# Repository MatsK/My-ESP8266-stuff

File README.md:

# My-ESP8266-stuff

## Concept

### Breakout board
The Breakout board is for the ESP-01 version of the ESP8266 and make it easy to connect a ESP-01 to a lab board.

### Programmer
The programmer board is used togheter with a 3,3 volt, USB-serial device.

### USB Power to lab board
This USB power for lab boards has a auto reset fuse that ensure that if it is shorten it will not destroy the USB port on the computer.

## Files:

### My ESP-01 Breakout board
- ESP8266_ESP-01_Breakout_2015-11-16 (.sch/.brd)

### ESP-12 Breakout SMT
- ESP-12_Breakout_SMT (.sch/.brd)

### ESP-01 Programmer
- ESP8266-Programmer_2015-11-16 (.sch/.brd)

### USB Micro Power to lab board
- USB_Micro_Power_to_lab_board_2015-11-16 (.sch/.brd)

## Picture of the different PCB
### My ESP-01 Breakout board

## ESP-12 Breakout SMT board

### ESP-01 Programmer

### USB Micro Power to lab board

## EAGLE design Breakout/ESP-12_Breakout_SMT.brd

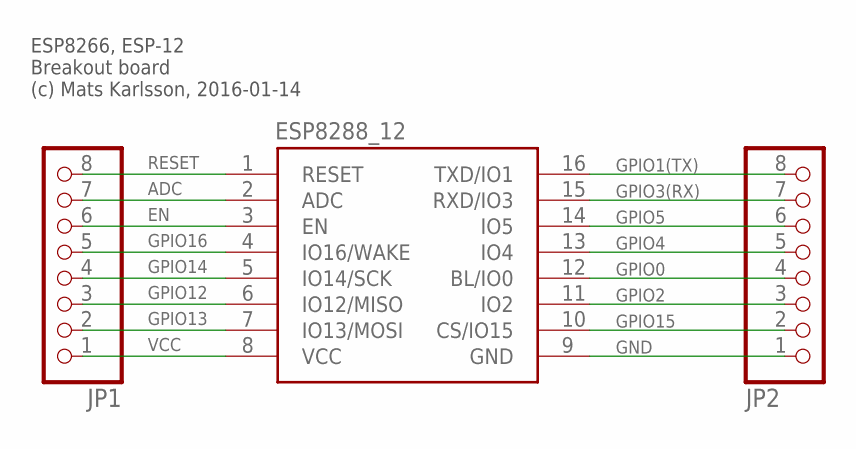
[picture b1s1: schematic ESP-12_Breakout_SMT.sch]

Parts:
ESP8288_12: ESP8266-12
JP1, JP2: PINHD-1X81X08_SMT; 1X08_SMT

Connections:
ADC: ESP8288_12.2 (ADC), JP1.7
EN: ESP8288_12.3 (EN), JP1.6
GND: ESP8288_12.9 (GND), JP2.1
GPIO0: ESP8288_12.12 (BL/IO0), JP2.4
GPIO1(TX): ESP8288_12.16 (TXD/IO1), JP2.8
GPIO2: ESP8288_12.11 (IO2), JP2.3
GPIO3(RX): ESP8288_12.15 (RXD/IO3), JP2.7
GPIO4: ESP8288_12.13 (IO4), JP2.5
GPIO5: ESP8288_12.14 (IO5), JP2.6
GPIO12: ESP8288_12.6 (IO12/MISO), JP1.3
GPIO13: ESP8288_12.7 (IO13/MOSI), JP1.2
GPIO14: ESP8288_12.5 (IO14/SCK), JP1.4
GPIO15: ESP8288_12.10 (CS/IO15), JP2.2
GPIO16: ESP8288_12.4 (IO16/WAKE), JP1.5
RESET: ESP8288_12.1 (RESET), JP1.8
VCC: ESP8288_12.8 (VCC), JP1.1

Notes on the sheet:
ESP8266, ESP-12 Breakout board (c) Mats Karlsson, 2016-01-14

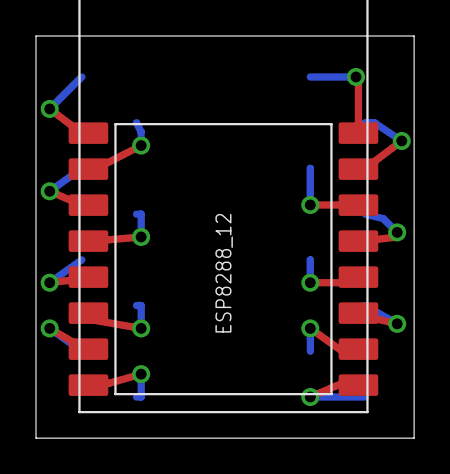
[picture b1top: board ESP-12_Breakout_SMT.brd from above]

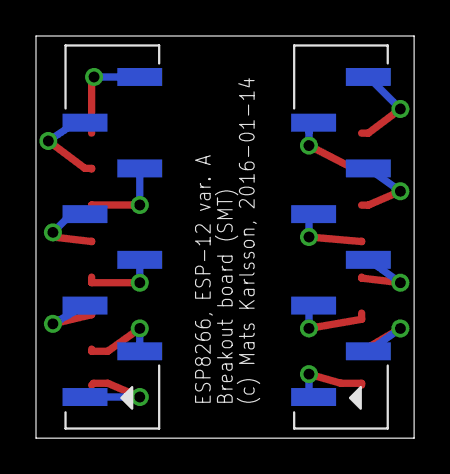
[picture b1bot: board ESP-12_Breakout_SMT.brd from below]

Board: 2 copper layers, 21.0 x 22.3 mm, 3 parts (2 on the bottom side), 16 nets.

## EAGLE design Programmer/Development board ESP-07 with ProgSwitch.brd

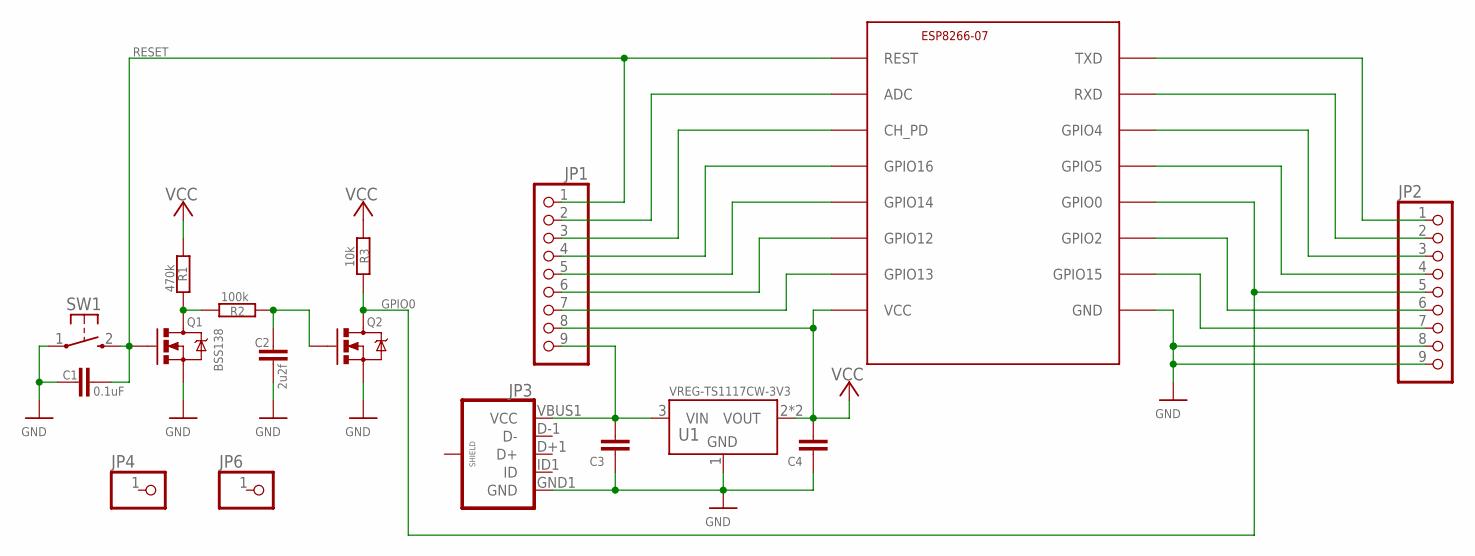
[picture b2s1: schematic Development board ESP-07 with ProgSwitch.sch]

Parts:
C1: 0.1uF; C025-024X044
C2: 2u2f; C025-024X044
C3, C4: C-EU025-024X044; C025-024X044
ESP8266-07: ESP8266-07; ESP-07
JP1, JP2: PINHD-1X91X09_SMT; 1X09_SMT
JP3: USB_MICROB_PLUGCONN-11752; USB-B-MICRO-SMD_V03
JP4, JP6: PINHD-1X1; 1X01
Q1, Q2: BSS138; SOT23-3
R1: 470k; R1206
R2: 100k; R1206
R3: 10k; R1206
SW1: KSS-2EG4430
U1: VREG-TS1117CW-3V3; SOT223

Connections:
GND: C1.1, C2.1, C3.1, C4.1, ESP8266-07.GND, JP2.8, JP2.9, JP3.GND1 (GND), Q1.2 (S), Q2.2 (S), SW1.1, U1.1 (GND)
GPIO0: ESP8266-07.GPIO0, JP2.5, Q2.3 (D), R3.2
unnamed: ESP8266-07.TXD, JP2.1
unnamed: ESP8266-07.RXD, JP2.2
unnamed: Q1.3 (D), R1.1, R2.1
unnamed: C2.2, Q2.1 (G), R2.2
unnamed: ESP8266-07.GPIO5, JP2.4
unnamed: ESP8266-07.VCC, JP1.8
unnamed: ESP8266-07.GPIO2, JP2.6
unnamed: ESP8266-07.GPIO15, JP2.7
unnamed: ESP8266-07.ADC, JP1.2
unnamed: ESP8266-07.CH_PD, JP1.3
unnamed: ESP8266-07.GPIO16, JP1.4
unnamed: ESP8266-07.GPIO14, JP1.5
unnamed: ESP8266-07.GPIO12, JP1.6
unnamed: C3.2, JP1.9, JP3.VBUS1 (VCC), U1.3 (VIN)
unnamed: ESP8266-07.GPIO13, JP1.7
unnamed: ESP8266-07.GPIO4, JP2.3
RESET: C1.2, ESP8266-07.REST, JP1.1, Q1.1 (G), SW1.2 (S)
VCC: C4.2, R1.2, R3.1, U1.2 (VOUT), U1.4 (VOUT)

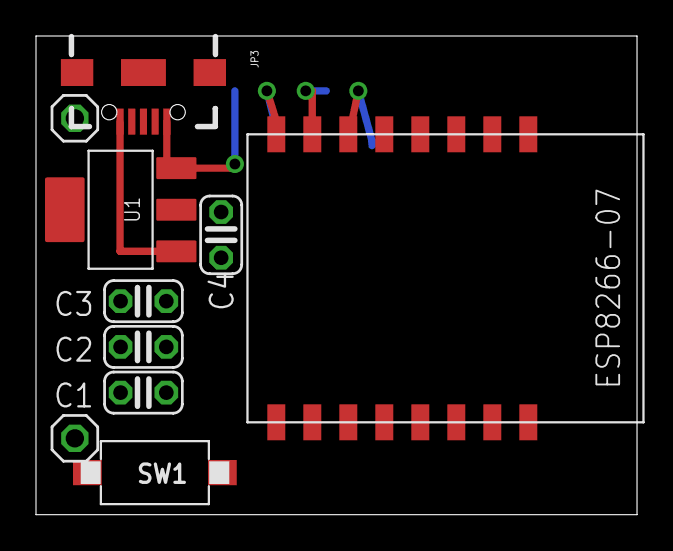
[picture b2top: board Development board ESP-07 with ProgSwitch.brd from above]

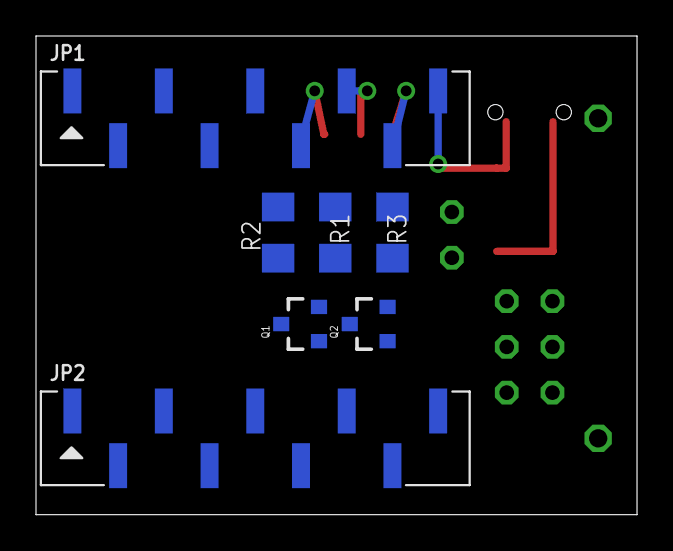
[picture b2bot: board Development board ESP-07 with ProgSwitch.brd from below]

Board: 2 copper layers, 33.4 x 26.6 mm, 17 parts (7 on the bottom side), 20 nets.

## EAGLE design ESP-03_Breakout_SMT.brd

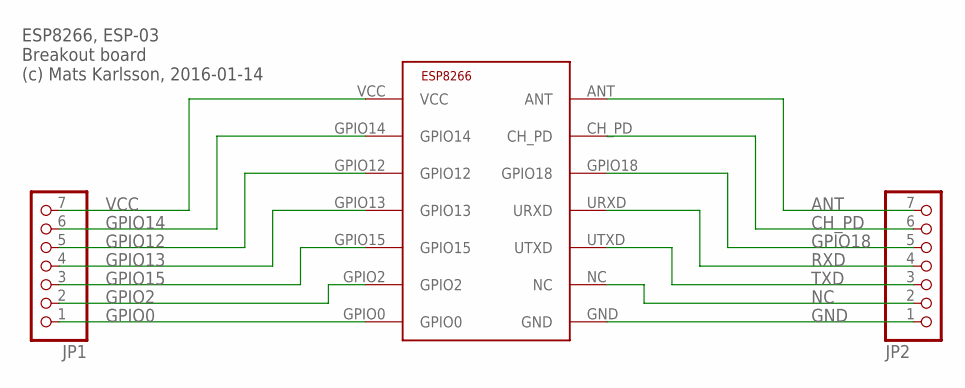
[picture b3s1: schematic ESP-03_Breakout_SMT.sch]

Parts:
JP1, JP2: PINHD-1X71X07_SMT; 1X07_SMT
U$1: ESP8266-03; ESP-03

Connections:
ANT: JP2.7, U$1.ANT
CH_PD: JP2.6, U$1.CH_PD
GND: JP2.1, U$1.GND
GPIO0: JP1.1, U$1.GPIO0
GPIO2: JP1.2, U$1.GPIO2
GPIO12: JP1.5, U$1.GPIO12
GPIO13: JP1.4, U$1.GPIO13
GPIO14: JP1.6, U$1.GPIO14
GPIO15: JP1.3, U$1.GPIO15
GPIO18: JP2.5, U$1.GPIO18
NC: JP2.2, U$1.NC
RXD: JP2.4, U$1.URXD
TXD: JP2.3, U$1.UTXD
VCC: JP1.7, U$1.VCC

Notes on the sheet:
ESP8266, ESP-03 Breakout board (c) Mats Karlsson, 2016-01-14

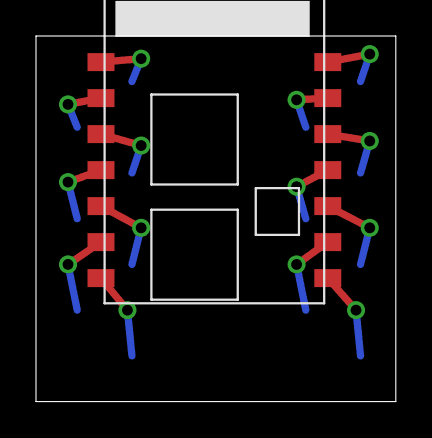
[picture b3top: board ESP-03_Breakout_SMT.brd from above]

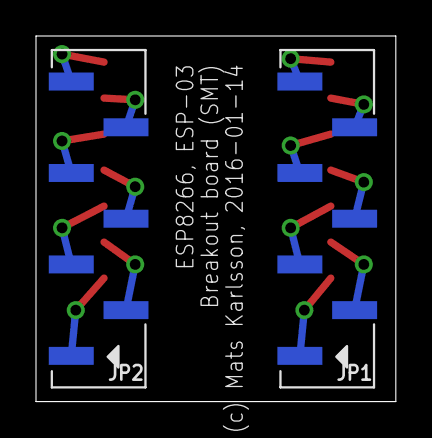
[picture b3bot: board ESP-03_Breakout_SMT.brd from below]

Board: 2 copper layers, 20.0 x 20.3 mm, 3 parts (2 on the bottom side), 14 nets.

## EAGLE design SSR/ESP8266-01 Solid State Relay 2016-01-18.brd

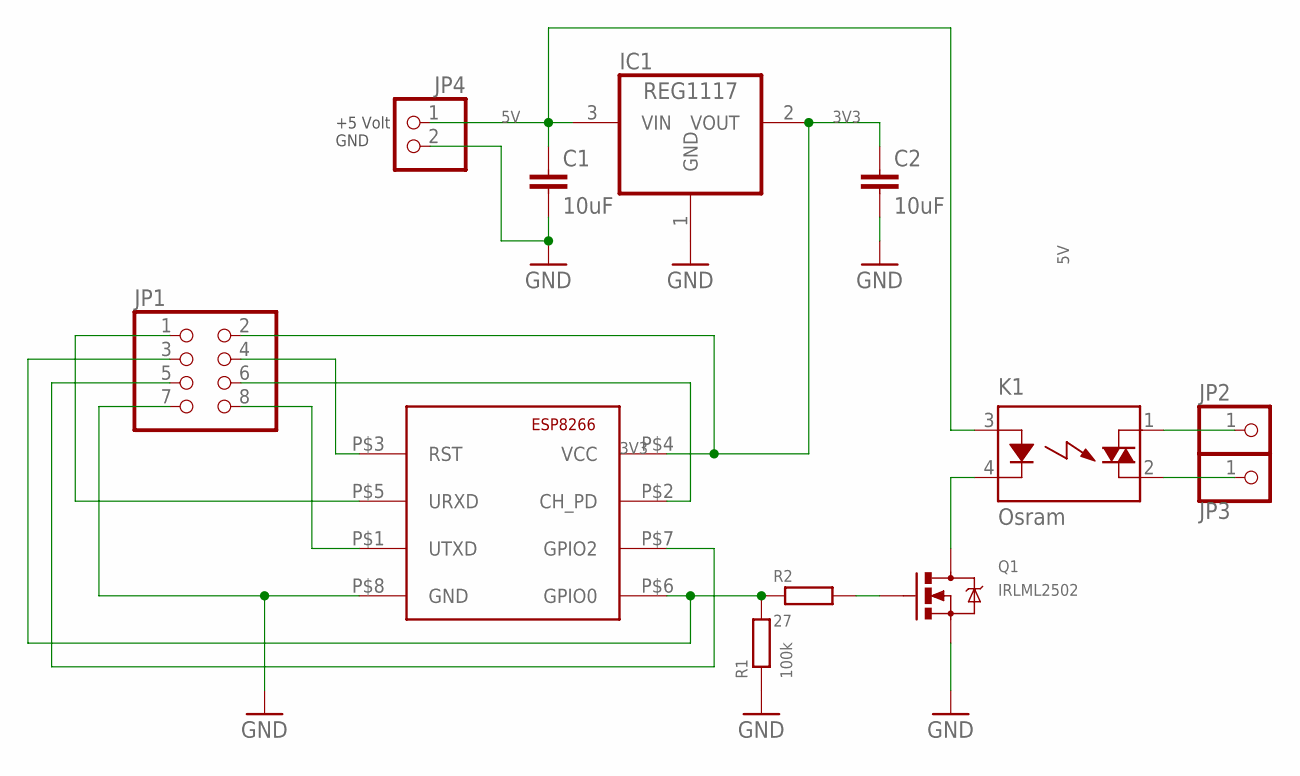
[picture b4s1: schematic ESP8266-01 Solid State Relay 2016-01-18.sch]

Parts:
C1, C2: 10uF; C1206
IC1: REG1117; SOT223
JP1: PINHD-2X4; 2X04
JP2, JP3: PINHD-1X1; 1X01
JP4: PINHD-1X2; 1X02
K1: Osram; S2XXEX
Q1: IRLML2502; SOT23-3
R1: 100k; R0805
R2: 27; R0805
U$1: ESP8266-01; ESP-01

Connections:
3V3: C2.1, IC1.2 (VOUT), JP1.2, U$1.P$4 (VCC)
5V: C1.1, IC1.3 (VIN), JP4.1, K1.3 (A)
GND: C1.2, C2.2, IC1.1 (GND), JP1.7, JP4.2, Q1.2 (S), R1.1, U$1.P$8 (GND)
unnamed: Q1.1 (G), R2.2
unnamed: JP1.4, U$1.P$3 (RST)
unnamed: K1.4 (K), Q1.3 (D)
unnamed: JP3.1, K1.2 (DS2)
unnamed: JP1.6, U$1.P$2 (CH_PD)
unnamed: JP1.8, U$1.P$1 (UTXD)
unnamed: JP1.1, U$1.P$5 (URXD)
unnamed: JP1.3, R1.2, R2.1, U$1.P$6 (GPIO0)
unnamed: JP1.5, U$1.P$7 (GPIO2)
unnamed: JP2.1, K1.1 (DS1)

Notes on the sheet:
+5 Volt GND

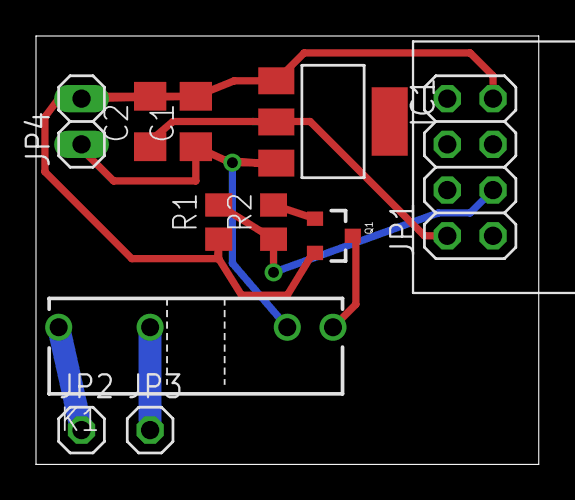
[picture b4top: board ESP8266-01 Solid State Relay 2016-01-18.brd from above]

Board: 2 copper layers, 27.9 x 23.8 mm, 12 parts (0 on the bottom side), 13 nets.

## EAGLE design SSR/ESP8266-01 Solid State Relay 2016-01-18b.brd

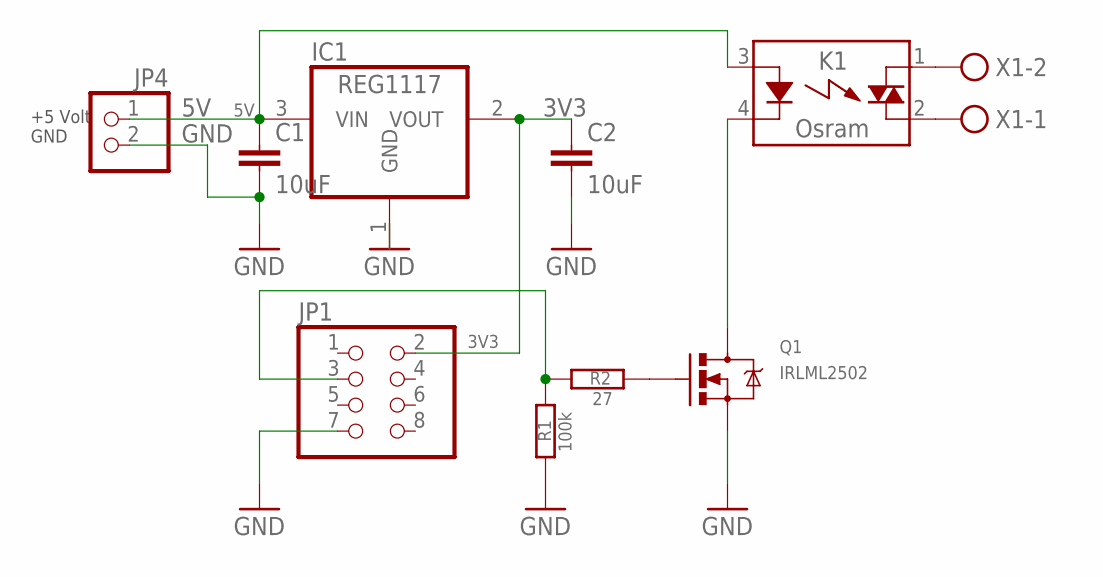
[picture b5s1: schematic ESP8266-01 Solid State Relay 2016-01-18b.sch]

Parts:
C1, C2: 10uF; C1206
IC1: REG1117; SOT223
JP1: PINHD-2X4; 2X04
JP4: PINHD-1X2; 1X02
K1: Osram; S2XXEX
Q1: IRLML2502; SOT23-3
R1: 100k; R0805
R2: 27; R0805
X1: W237-102

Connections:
3V3: C2.1, IC1.2 (VOUT), JP1.2
5V: C1.1, IC1.3 (VIN), JP4.1, K1.3 (A)
GND: C1.2, C2.2, IC1.1 (GND), JP1.7, JP4.2, Q1.2 (S), R1.1
unnamed: Q1.1 (G), R2.2
unnamed: K1.2 (DS2), X1.1
unnamed: K1.4 (K), Q1.3 (D)
unnamed: K1.1 (DS1), X1.2
unnamed: JP1.3, R1.2, R2.1

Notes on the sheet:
+5 Volt GND

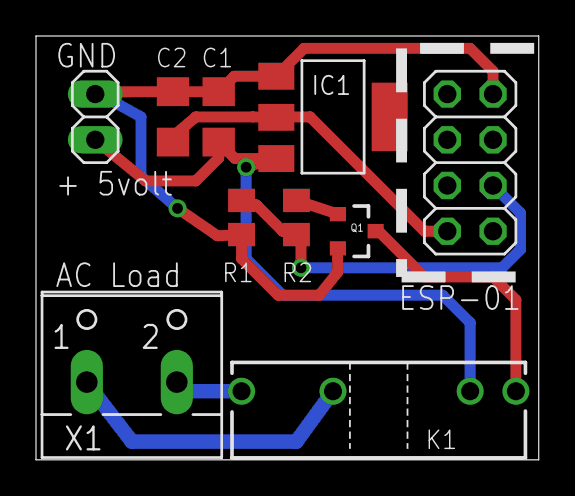
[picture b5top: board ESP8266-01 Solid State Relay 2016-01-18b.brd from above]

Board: 2 copper layers, 27.9 x 23.5 mm, 10 parts (0 on the bottom side), 8 nets.

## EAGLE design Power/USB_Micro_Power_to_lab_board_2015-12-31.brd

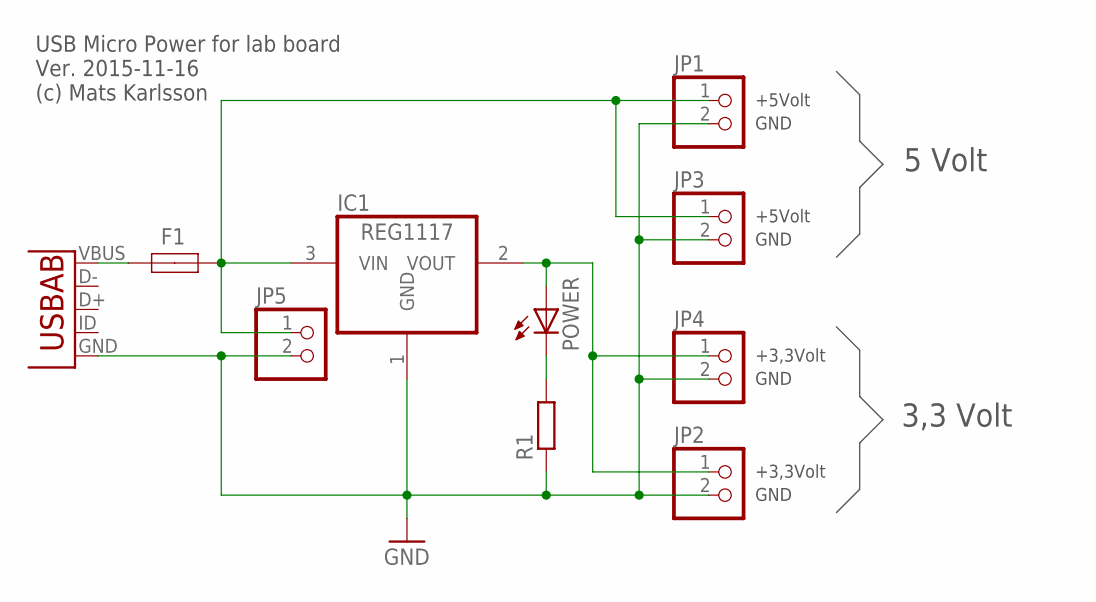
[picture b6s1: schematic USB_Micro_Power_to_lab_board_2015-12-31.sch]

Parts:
F1: LITTELFUSE_1812_500MA; R1812
IC1: REG1117; SOT223
JP1, JP2, JP3, JP4, JP5: PINHD-1X2; 1X02
POWER: LED3MM
R1: R-EU_0204/5; 0204/5
U1: USB-ABUSB-AB-MICRO-SMD; USB-AB-MICRO-SMD_VO2

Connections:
GND: IC1.1 (GND), JP1.2, JP2.2, JP3.2, JP4.2, JP5.2, R1.1, U1.GND
unnamed: F1.2, IC1.3 (VIN), JP1.1, JP3.1, JP5.1
unnamed: F1.1, U1.VBUS
unnamed: POWER.K (C), R1.2
unnamed: IC1.2 (VOUT), JP2.1, JP4.1, POWER.A

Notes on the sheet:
GND
+3,3Volt
+5Volt
5 Volt
3,3 Volt
USB Micro Power for lab board Ver. 2015-11-16 (c) Mats Karlsson

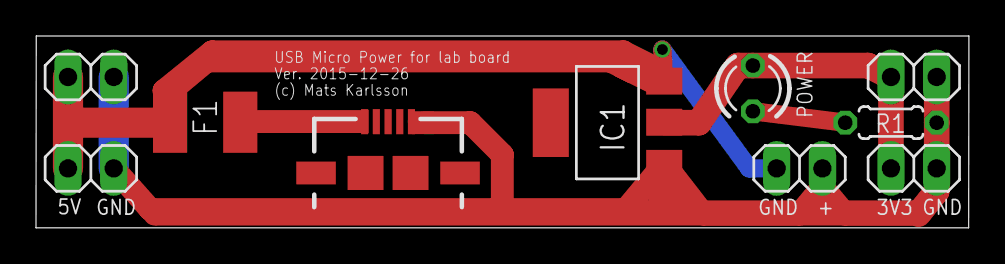
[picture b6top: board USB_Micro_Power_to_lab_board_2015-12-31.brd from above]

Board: 2 copper layers, 51.8 x 10.7 mm, 10 parts (0 on the bottom side), 5 nets.

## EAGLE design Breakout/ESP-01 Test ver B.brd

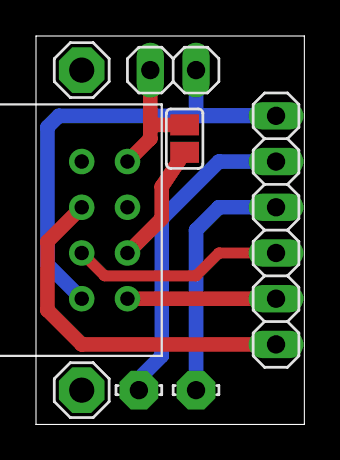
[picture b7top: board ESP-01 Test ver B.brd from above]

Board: 2 copper layers, 14.9 x 21.6 mm, 8 parts (0 on the bottom side), 8 nets.

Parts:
JP1: 1X02
JP2: 1X06
LSP1, LSP2: SE14
LSP3, LSP4: LSP10
SJ1: SJ
U$1: ESP8266-01; ESP-01

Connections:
GND: JP1.2, JP2.6, U$1.P$8
unnamed: JP2.2, U$1.P$1
unnamed: SJ1.1, U$1.P$2
unnamed: JP1.1, SJ1.2, U$1.P$4
unnamed: JP2.3, U$1.P$7
unnamed: JP2.1, U$1.P$6
unnamed: JP2.5, LSP4.MP
unnamed: JP2.4, LSP3.MP

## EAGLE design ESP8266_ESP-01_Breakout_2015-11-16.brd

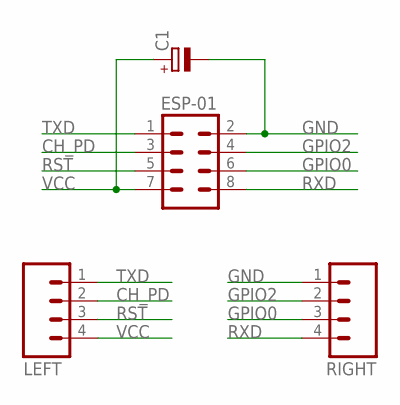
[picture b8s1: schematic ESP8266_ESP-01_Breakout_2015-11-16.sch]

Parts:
C1: CPOL-EUB45181B; B45181B
ESP-01: M04X2; 2X4
LEFT: M04LONGPADS; 1X04_LONGPADS
RIGHT: M04LONGPADS; 1X04_LONGPADS

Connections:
CH_PD: ESP-01.3, LEFT.2
GND: C1.-, ESP-01.2, RIGHT.1
GPIO0: ESP-01.6, RIGHT.3
GPIO2: ESP-01.4, RIGHT.2
RST: ESP-01.5, LEFT.3
RXD: ESP-01.8, RIGHT.4
TXD: ESP-01.1, LEFT.1
VCC: C1.+, ESP-01.7, LEFT.4

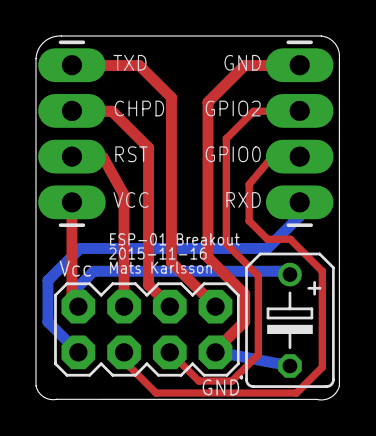
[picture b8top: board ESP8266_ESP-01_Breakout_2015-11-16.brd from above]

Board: 2 copper layers, 16.9 x 20.2 mm, 4 parts (0 on the bottom side), 8 nets.

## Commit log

2015-11-16 Initial files
    First
2015-11-16 Added picture of the breakout board.
2015-11-16 Added info
2015-11-16 Added ESP8266 Programmer v3
2015-11-16 New readme
2015-11-16 Fine tuning of programmer and larger Pads for the breakout board
    Fine tuning of programmer and larger Pads for the breakout board
2015-11-16 New PCB shoots
2015-11-16 Cleanup
2015-11-16 Screenshot of PCB
    USB_Micro_Power_to_lab_board_2015-11-16.png
2015-11-16 Updated text
2015-12-11 Structural change
2015-12-30 Upgrades
    Small changes
2015-12-30 New ignore
2015-12-31 Improvements
2015-12-31 Added .gitignore
2015-12-31 Correction of .getignore
2015-12-31 Addded eagle to gitignore
2016-01-24 Minor cosmetic changes
2016-02-20 New boards

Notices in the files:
parts and their libraries:
SparkFun-Connectors: Licensing: CC v3.0 Share-Alike You are welcome to use this library for commercial purposes.
SparkFun-DiscreteSemi: Licensing: Creative Commons ShareAlike 4.0 International - https://creativecommons.org/licenses/by-sa/4.0
